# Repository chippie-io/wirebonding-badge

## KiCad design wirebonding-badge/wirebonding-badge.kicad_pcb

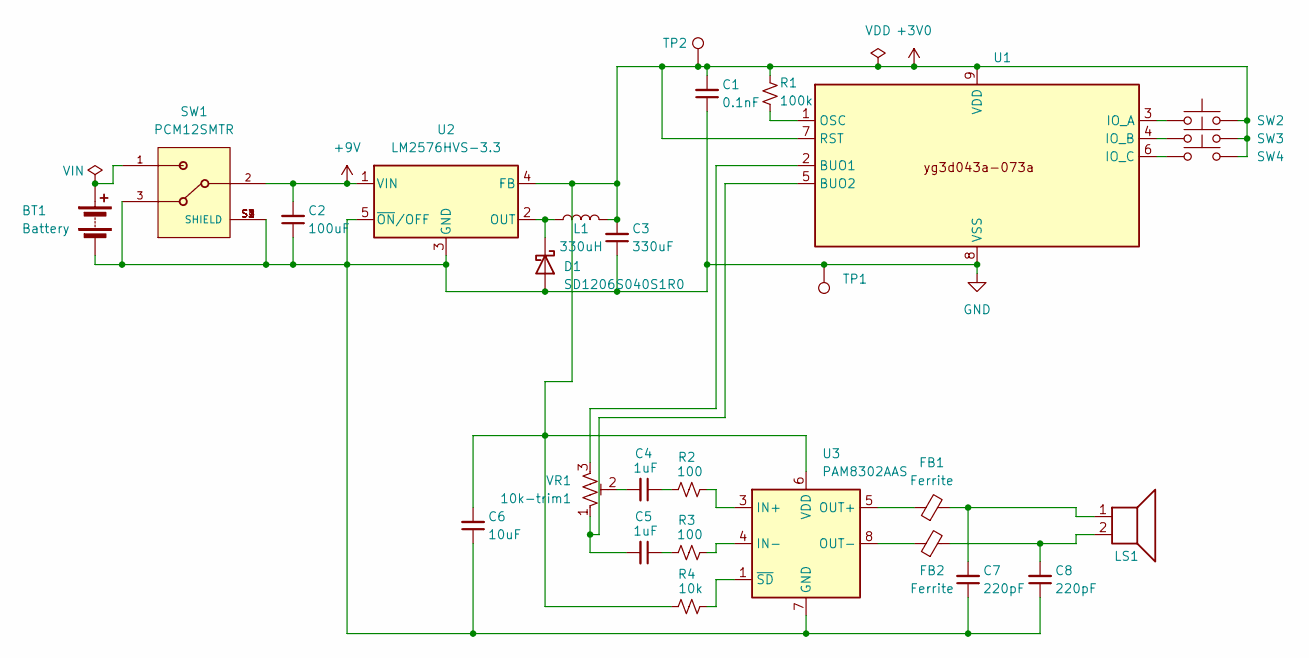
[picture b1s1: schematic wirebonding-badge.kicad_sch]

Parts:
10k-trim1: VR1; TRIM_TC33X-2-102E
BT1: Battery; BatteryHolder_MPD_BA9VPC_1xPP3
C1: 0.1nF; C_1206_3216Metric
C2: 100uF; C_1206_3216Metric
C3: 330uF; C_1206_3216Metric
C4, C5: 1uF; C_1206_3216Metric
C6: 10uF; C_1206_3216Metric
C7, C8: 220pF; C_1206_3216Metric
D1: SD1206S040S1R0; D_1206_3216Metric_Pad1.42x1.75mm_HandSolder
FB1, FB2: Ferrite; L_1206_3216Metric_Pad1.22x1.90mm_HandSolder
L1: 330uH; L_1206_3216Metric_Pad1.22x1.90mm_HandSolder
LS1: Speaker; same_sky_speaker_mix
R1: 100k; R_1206_3216Metric
R2, R3: 100; R_1206_3216Metric
R4: 10k; R_1206_3216Metric
SW1: PCM12SMTR; SW_PCM12SMTR
SW2, SW3, SW4: SW_Push; SW_Push_1TS009xxxx-xxxx-xxxx_6x6x5mm
TP1, TP2: TestPoint; TestPoint_Keystone_5019_Minature
U1: die-yg3d043a-073a
U2: LM2576HVS-3.3; TO-263-5_TabPin3
U3: PAM8302AAS; MSOP-8_3x3mm_P0.65mm

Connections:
+3V0: C1.2, C3.2, C6.2, L1.2, R1.1, R4.1, SW2.2, SW3.2, SW4.2, TP2.1, U1.7 (RST), U1.9 (VDD), U2.4 (FB), U3.6 (VDD)
+9V: C2.2, SW1.2, U2.1 (VIN)
GND: BT1.2 (-), C1.1, C2.1, C3.1, C6.1, C7.1, C8.1, D1.2 (A), SW1.3, SW1.S1 (SHIELD), SW1.S2 (SHIELD), SW1.S3 (SHIELD), SW1.S4 (SHIELD), TP1.1, U1.8 (VSS), U2.3 (GND), U2.5 (~ON/OFF), U3.7 (GND)
unnamed: 10k-trim1.2, C4.2
unnamed: BT1.1 (+), SW1.1
unnamed: C4.1, R2.1
unnamed: C5.1, R3.1
unnamed: C7.2, FB1.2, LS1.1
unnamed: C8.2, FB2.2, LS1.2
unnamed: D1.1 (K), L1.1, U2.2 (OUT)
unnamed: 10k-trim1.3, U1.2 (BUO1)
unnamed: 10k-trim1.1, C5.2, U1.5 (BUO2)
unnamed: SW2.1, U1.3 (IO_A)
unnamed: SW3.1, U1.4 (IO_B)
unnamed: SW4.1, U1.6 (IO_C)
unnamed: R1.2, U1.1 (OSC)
unnamed: R2.2, U3.3 (IN+)
unnamed: R3.2, U3.4 (IN-)
unnamed: FB1.1, U3.5 (OUT+)
unnamed: FB2.1, U3.8 (OUT-)
unnamed: R4.2, U3.1 (~SD)

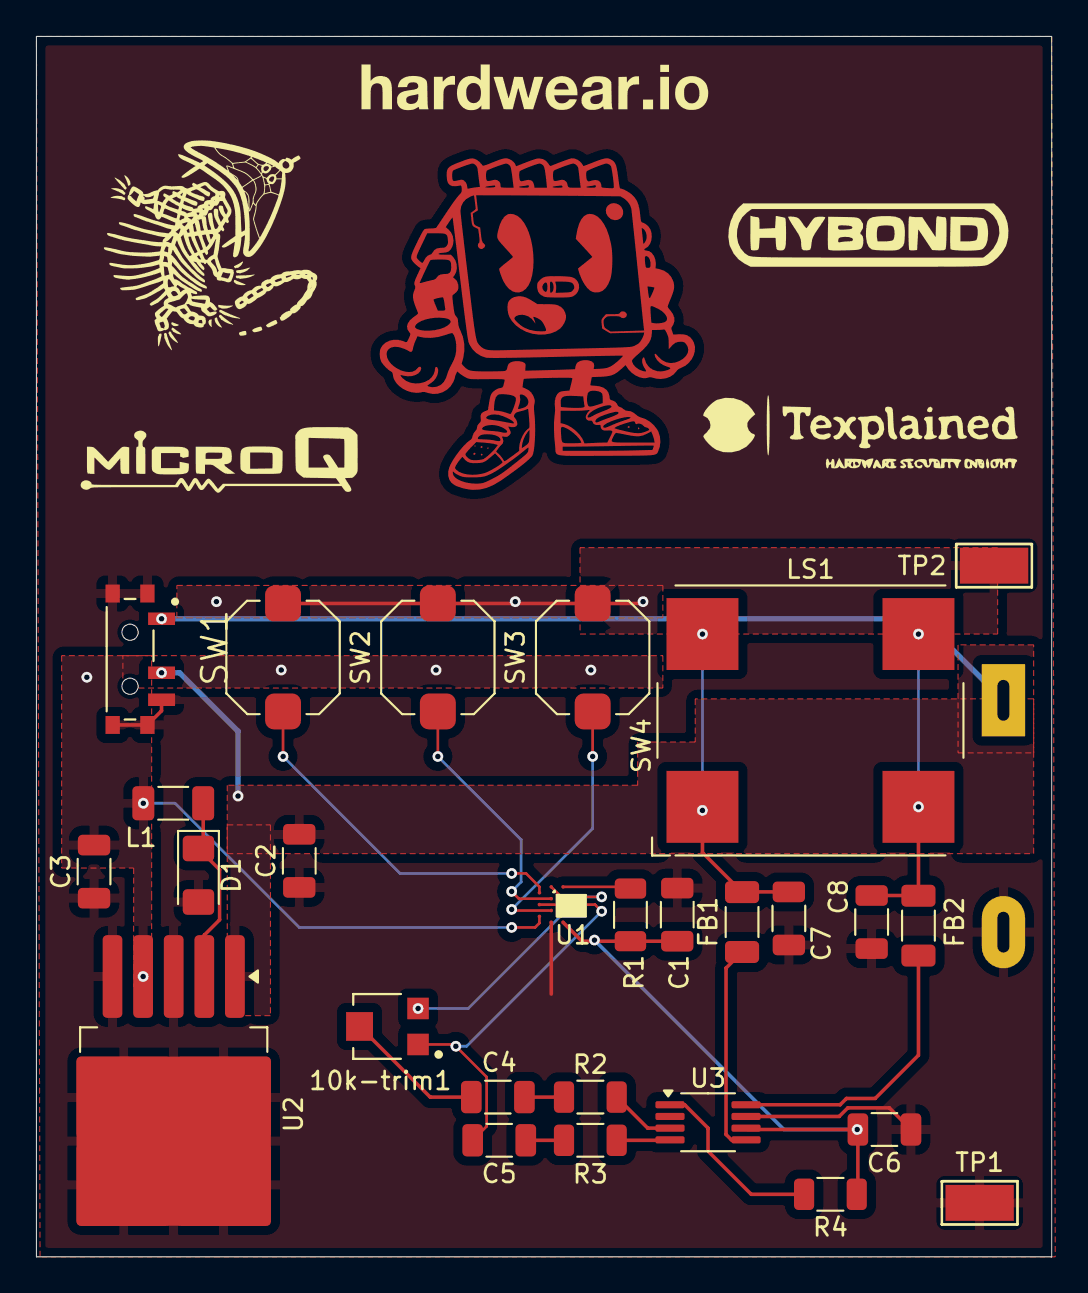
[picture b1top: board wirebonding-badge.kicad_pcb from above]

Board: 2 copper layers, 56.4 x 67.8 mm, 28 parts (1 on the bottom side), 21 nets.

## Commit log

2025-02-27 Added die research.
2025-02-27 Added initial badge layout. BOM hasn't been finalized yet.
2025-02-27 Finished connections. Ready for prototyping.
2025-05-13 Final revision for 5/2025.
2025-11-14 Add files via upload
    Added wire bond image.
2025-11-14 Rename image-3.png to wirebonded.png
